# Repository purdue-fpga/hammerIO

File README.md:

### Deploy to GH Pages
```
sudo apt install mkdocs-material 
pip install ghp-import \ mkdocs-material-extensions \ pymdown-extensions
make
```

### Run locally in Docker
```
docker compose up
```

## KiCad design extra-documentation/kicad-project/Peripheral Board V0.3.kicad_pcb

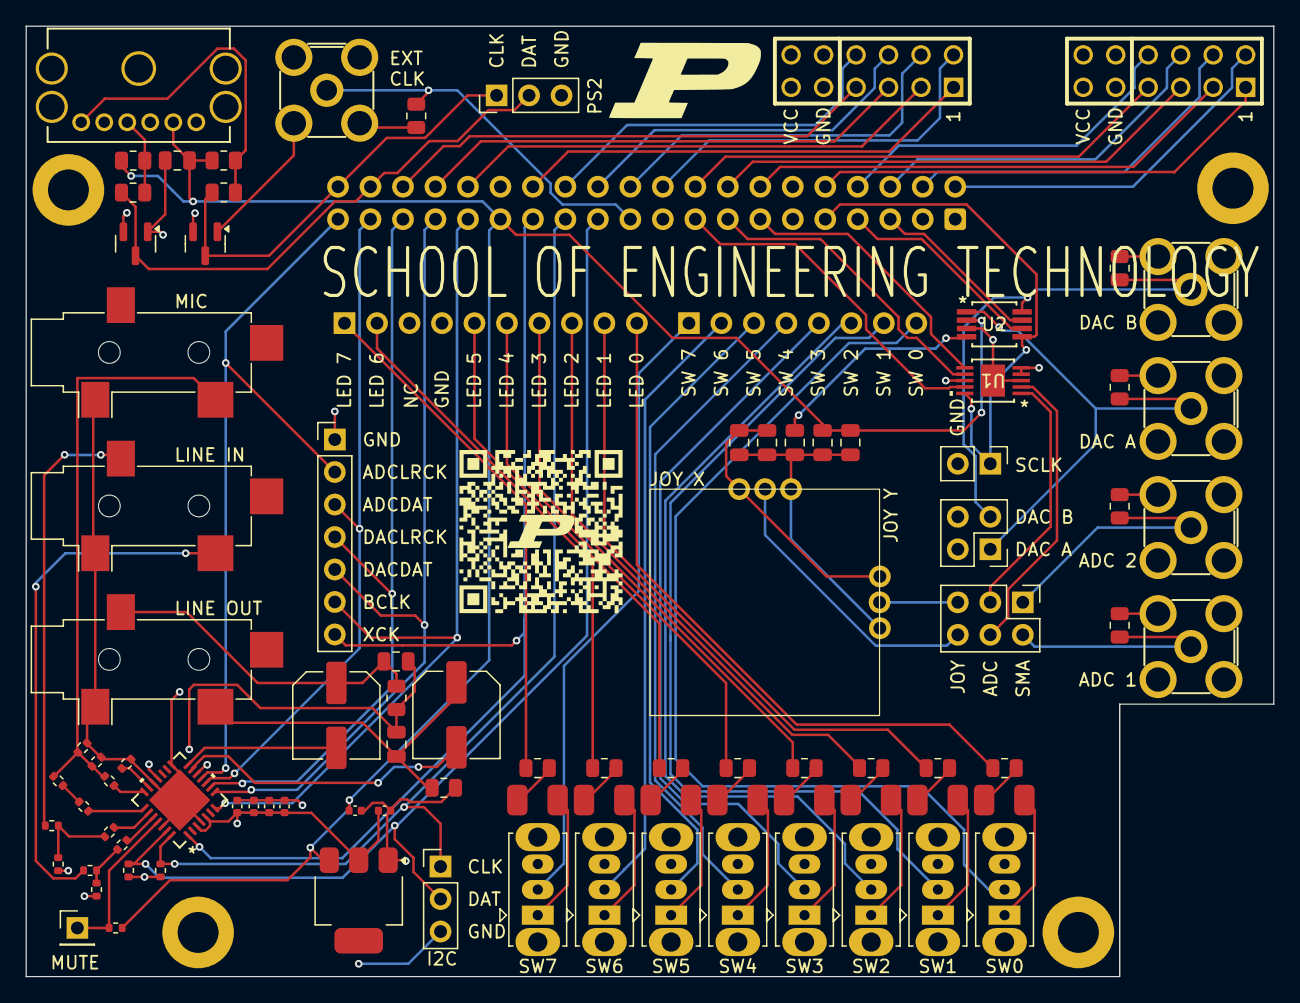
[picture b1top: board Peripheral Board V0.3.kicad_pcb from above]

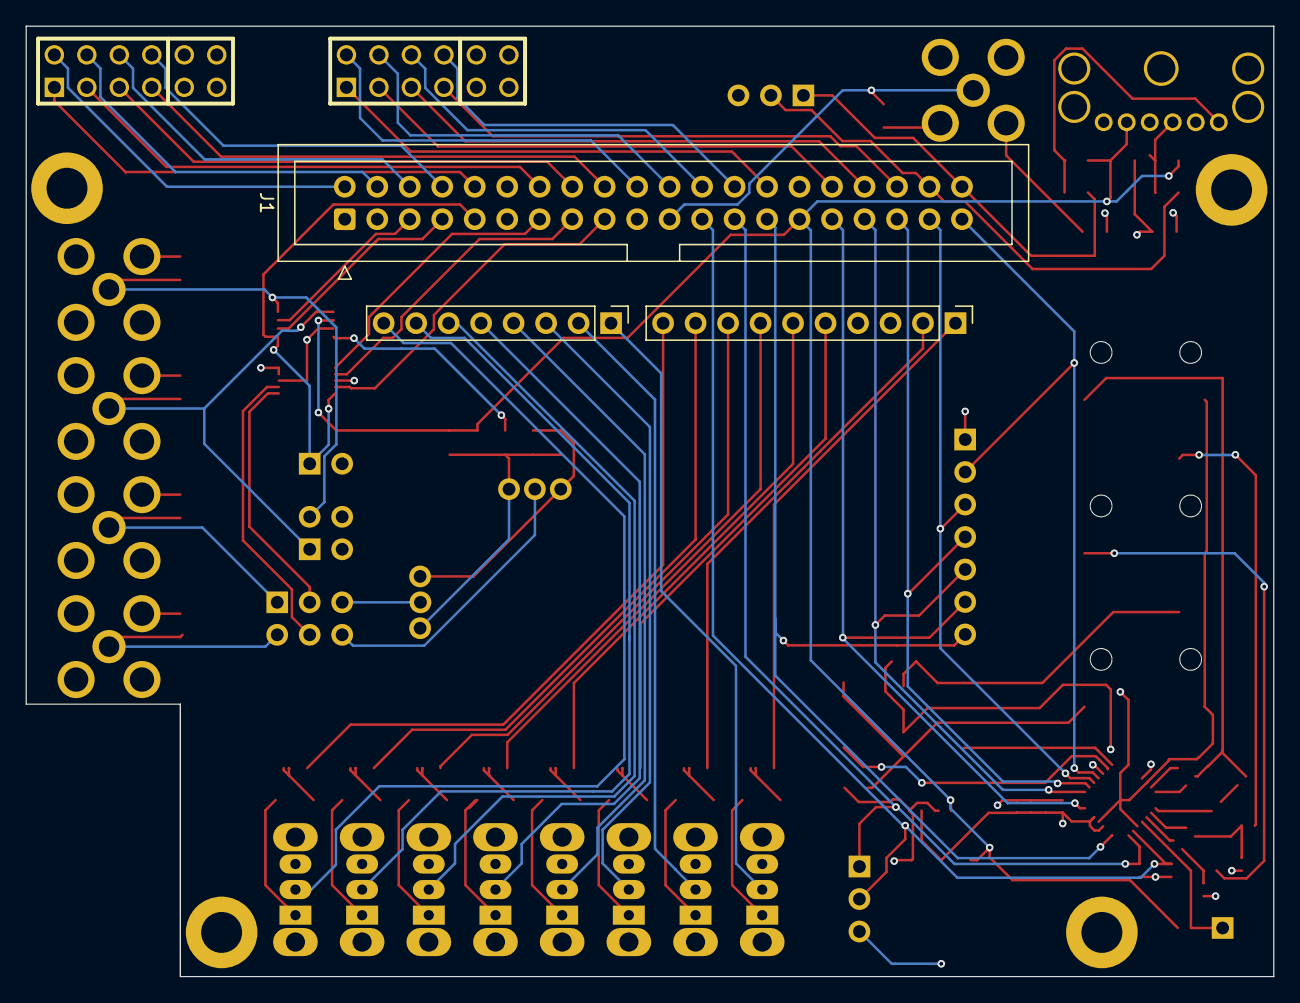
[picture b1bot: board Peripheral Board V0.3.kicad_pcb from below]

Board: 4 copper layers, 97.6 x 74.3 mm, 94 parts (3 on the bottom side), 88 nets.

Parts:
C1, C2, C3, C20: 0.1uF; C_0805_2012Metric
C4, C21: 10uF; C_0805_2012Metric
C5, C9, C10, C11: 0.1uF; C_0402_1005Metric
C6: 10uF; R_0402_1005Metric
C7, C8: 1uF; C_0402_1005Metric
C12, C13, C14: 1uF; R_0402_1005Metric
C15: 1000pF; R_0402_1005Metric
C16, C17: 220uF; C_Elec_6.3x7.7
C18, C19: 220pF; C_0805_2012Metric
D0, D1, D2, D3, D4, D5, D6, D7: LED; 150141AS73100-LED
D9, D10: BAT54S; SOT-23
J1: 2x20 GPIO header; IDC-Header_2x20_P2.54mm_Vertical
J2, J3: Conn_02x06_Counter_Clockwise; pmod
J4: Conn_02x02_Top_Bottom; PinHeader_2x02_P2.54mm_Vertical
J5: Mini-DIN-6; KMDTX-HT-6S-BSC_KYC
J6: Conn_02x03_Top_Bottom; PinHeader_2x03_P2.54mm_Vertical
J7: Conn_01x01; PinHeader_1x01_P2.54mm_Vertical
J8_1: Conn_01x10; PinHeader_1x10_P2.54mm_Vertical
J8_2: Conn_01x08; PinHeader_1x08_P2.54mm_Vertical
J9: EXT_CLK_IN; CONN_PCB.SMAFRA_TAL
J9-line-in1, J9-line-out1, J9-mic-in1: SJ-3524-SMT-BE; Jack_3.5mm_CUI_SJ-3524-SMT_Horizontal_fixed
J10: SCLK testpoint; PinHeader_1x02_P2.54mm_Vertical
J11: ADC_IN_1; CONN_PCB.SMAFRA_TAL
J12: ADC_IN_2; CONN_PCB.SMAFRA_TAL
J13: DAC_OUT_A; CONN_PCB.SMAFRA_TAL
J14: DAC_OUT_B; CONN_PCB.SMAFRA_TAL
J18: I2C_testpoint; PinHeader_1x03_P2.54mm_Vertical
J19: AUD_testpoint; PinHeader_1x07_P2.54mm_Vertical
J20: PS2_testpoint; PinHeader_1x03_P2.54mm_Vertical
R0, R1, R2, R3, R4, R5, R6, R7: 680; R_0805_2012Metric
R9, R10: 2k; R_0805_2012Metric
R11, R12: 120; R_0805_2012Metric
R13, R14, R15: 2k; R_0402_1005Metric
R16, R17, R18, R19: 4.7k; R_0402_1005Metric
R20: 330; R_0402_1005Metric
R21: 680; R_0402_1005Metric
R22: 47k; R_0402_1005Metric
R23, R24: 47k; R_0805_2012Metric
R25, R26, R27, R28, R29: 1k; R_0805_2012Metric
SW0, SW1, SW2, SW3, SW4, SW5, SW6, SW7: SW_SPDT; SW_Slide_SPDT_Straight_CK_OS102011MS2Q
U1: MAX11664 ADC; 21-0109D_MXM
U2: AD7303 DAC; RM_8_ADI
U3: SSM2603 audio codec; CP_28_4_ADI
U4: Adafruit2765
U5: TLV1117-33; SOT-223

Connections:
+3.3V: C20.2, C21.2, D9.2 (K), D10.2 (K), J1.11, J2.6, J2.12, J3.6, J3.12, SW0.3 (C), SW1.3 (C), SW2.3 (C), SW3.3 (C), SW4.3 (C), SW5.3 (C), SW6.3 (C), SW7.3 (C), U1.4 (REF), U1.5 (VDD), U1.8 (OVDD), U4.3 (Vref), U4.6 (Vref)
+3.3VA: C5.2, C7.2, C9.2, C10.2, C11.2, R14.2, R15.2, U3.3 (DCVDD), U3.5 (DBVDD), U3.12 (HPVDD), U3.18 (AVDD), U5.2 (VO)
+5V: C2.2, C3.2, C4.2, C8.2, J1.29, J5.5, R9.2, R10.2, R13.2, U2.2 (VDD), U5.3 (VI)
/ADC_CHSEL: J1.15, U1.7 (CHSEL)
/ADC_CS: J1.13, U1.6 (*CS)
/ADC_DOUT: J1.17, U1.9 (DOUT)
/ADC_IN_1: J6.2, J11.1, R29.2
/ADC_IN_2: J6.1, J12.1, R26.2
/AUD_ADCDAT: J1.37, J19.3, U3.10 (RECDAT)
/AUD_ADCLRCK: J1.39, J19.2, U3.11 (RECLRC)
/AUD_BCLK: J1.31, J19.6, U3.7 (BCLK)
/AUD_DACDAT: J1.33, J19.5, U3.8 (PBDAT)
/AUD_DACLRCK: J1.35, J19.4, U3.9 (PBLRC)
/AUD_XCK: J1.27, J19.7, U3.1 (MCLK/XTI)
/CLK: J5.6, R10.1, R11.1
/DAC_DIN: J1.7, U2.6 (DIN)
/DAC_OUT_A: J4.1, J13.1, R27.2, U2.1 (VOUTA)
/DAC_OUT_B: J4.3, J14.1, R28.2, U2.8 (VOUTB)
/DAC_SYNC: J1.5, U2.7 (SYNC*)
/Data: J5.1, R9.1, R12.1
/EXT_CLK: J1.21, J9.1, R25.2
/I2C_SCLK: J1.25, J18.1, R14.1, U3.28 (SCLK)
/I2C_SDAT: J1.23, J18.2, R15.1, U3.27 (SDIN)
/LED0: J8_1.1, R0.1
/LED1: J8_1.2, R1.1
/LED2: J8_1.5, R2.1
/LED3: J8_1.6, R3.1
/LED4: J8_1.7, R4.1
/LED5: J8_1.8, R5.1
/LED6: J8_1.9, R6.1
/LED7: J8_1.10, R7.1
/L_line_in: J9-line-in1.2 (T), R18.2
/L_line_out: C17.1, C18.1, J9-line-out1.2, R23.2
/PMOD_00_00: J1.20, J2.7
/PMOD_00_01: J1.22, J2.8
/PMOD_00_02: J1.24, J2.9
/PMOD_00_03: J1.26, J2.10
/PMOD_00_04: J1.28, J2.1
/PMOD_00_05: J1.32, J2.2
/PMOD_00_06: J1.34, J2.3
/PMOD_00_07: J1.36, J2.4
/PMOD_01_00: J1.2, J3.7
/PMOD_01_01: J1.4, J3.8
/PMOD_01_02: J1.6, J3.9
/PMOD_01_03: J1.8, J3.10
/PMOD_01_04: J1.10, J3.1
/PMOD_01_05: J1.14, J3.2
/PMOD_01_06: J1.16, J3.3
/PMOD_01_07: J1.18, J3.4
/PS2_CLK: D9.3 (COM), J1.40, J20.1, R11.2
/PS2_DAT: D10.3 (COM), J1.38, J20.2, R12.2
/R_line_in: J9-line-in1.3 (R), R19.2
/R_line_out: C16.1, C19.1, J9-line-out1.3, R24.2
/SCLK: J1.9, J10.1, U1.10 (SCLK), U2.5 (SCLK)
/SW0: J8_2.1, SW7.2 (B)
/SW1: J8_2.2, SW6.2 (B)
/SW2: J8_2.3, SW5.2 (B)
/SW3: J8_2.4, SW4.2 (B)
/SW4: J8_2.5, SW3.2 (B)
/SW5: J8_2.6, SW2.2 (B)
/SW6: J8_2.7, SW1.2 (B)
/SW7: J8_2.8, SW0.2 (B)
/mic_in: C14.1, C15.2, J9-mic-in1.2, R21.2, R22.2
GND: C1.1, C2.1, C3.1, C4.1, C5.1, C6.1, C7.1, C8.1, C9.1, C10.1, C11.1, C15.1, C18.2, C19.2, C20.1, C21.1, D0.1 (K), D1.1 (K), D2.1 (K), D3.1 (K), D4.1 (K), D5.1 (K), D6.1 (K), D7.1 (K), D9.1 (A), D10.1 (A), J1.12, J1.30, J2.5, J2.11, J3.5, J3.11, J4.2, J4.4, J5.3, J8_1.4, J9.2, J9.3, J9.4, J9.5, J9-line-in1.1 (S), J9-line-out1.1, J9-mic-in1.1, J10.2, J11.2, J11.3, J11.4, J11.5, J12.2, J12.3, J12.4, J12.5, J13.2, J13.3, J13.4, J13.5, J14.2, J14.3, J14.4, J14.5, J18.3, J19.1, J20.3, R16.1, R17.1, R22.1, R23.1, R24.1, R25.1, R26.1, R27.1, R28.1, R29.1, SW0.1 (A), SW1.1 (A), SW2.1 (A), SW3.1 (A), SW4.1 (A), SW5.1 (A), SW6.1 (A), SW7.1 (A), U1.3 (AGND), U1.11 (EPAD), U2.3 (GND), U3.4 (DGND), U3.15 (PGND), U3.19 (AGND), U3.26 (CSB), U3.29 (EP), U4.1 (gnd), U4.4 (gnd), U5.1 (GND)
unnamed: C12.1, R17.2, R18.1
unnamed: C13.1, R16.2, R19.1
unnamed: C14.2, R20.2
unnamed: D0.2 (A), R0.2
unnamed: D1.2 (A), R1.2
unnamed: D2.2 (A), R2.2
unnamed: D3.2 (A), R3.2
unnamed: D4.2 (A), R4.2
unnamed: D5.2 (A), R5.2
unnamed: D6.2 (A), R6.2
unnamed: D7.2 (A), R7.2
unnamed: J6.3, U1.1 (AIN1)
unnamed: J6.4, U1.2 (AIN2)
unnamed: J6.5, U4.2 (xRead)
unnamed: J6.6, U4.5 (yRead)
unnamed: J7.1, R13.1, U3.25 (MUTE)
unnamed: C1.2, U2.4 (REF)
unnamed: C17.2, U3.13 (LHPOUT)
unnamed: C12.2, U3.24 (LLINEIN)
unnamed: R21.1, U3.21 (MICBIAS)
unnamed: R20.1, U3.22 (MICIN)
unnamed: C16.2, U3.14 (RHPOUT)
unnamed: C13.2, U3.23 (RLINEIN)
unnamed: C6.2, U3.20 (VMID)

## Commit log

2025-04-08 first setup
2025-04-08 theme stufff
2025-04-08 logo and theme
2025-04-08 Update documentation
2025-04-08 github action + gh pages
2025-04-08 Delete gh-pages.yml
    nope
2025-04-08 Create Makefile
2025-04-08 logo change on dark mode
2025-04-10 mac changes
2025-04-10 mkdocs
2025-04-10 added font, prob wont use
2025-04-22 table support
2025-04-22 added pinout table
2025-04-22 file rename
2025-04-24 created page layout
2025-04-25 added individual pages for parts
2025-04-25 add pdf, try pdf embed
2025-04-29 updated from manual
2025-04-29 update from user manual, added files
2025-04-29 about
2025-04-29 added direct pdf links
2025-05-28 Update mkdocs.yml
    new hammerIO name
2025-05-28 Update index.md
    hammerio
